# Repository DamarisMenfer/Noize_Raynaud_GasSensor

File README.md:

# MOSH
#### Arduino Project in 5th year ISS at INSA Toulouse

## Overview
This repository contains the work produced during the course of Microcontroler and Open-Source Hardware (MOSH) of the 5th year Innovative Smart Systems (ISS) at INSA Toulouse. This work was produced by Alex Noize and Mathieu Raynaud.

The aim of this project was to design a complete PCB (Printed Circuit Board) implementing a double layer transimpedance amplificator assembly. This circuit is then used plugged to an Arduino board and a LoRa antenna to collect data from a gaz sensor and send it through a LoRa network.

## Project location
The project is located [here](https://github.com/AlexNoize/MOSH/tree/master/KiCad/Shield_Gas_Sensor/Shield_Gas_Sensor_Final).

## PCB schematic
Let's first have a look to the electrical circuit:

On the center of the image, the double layer transimpedance circuit implements several functionalities: 
* On the left of the scheme, the entry resistor (R1) protect the operational amplifier from the electrostatic discharges, and is associated to the C1 capacitor to filter the voltage noise.
* The C1 capacitor is also associated to the R2 resistor to filter the current noise.
* The R3 resistor is used to adapt our assembly to the correct calibre.
* At the output of the amplifier, the C2 capacitor is associated to the R4 resistor to create an active filter.
* Then, the R5 resistor and the C4 capacitor constitute a low-pass filter at the output of the assembly.
* Finally, the C3 capacitor filter the noise coming from the 5V voltage input.

We also have 3 other schemes on the picture which are:
* The RN2483 LoRa transceiver scheme on the left-top of the scheme
* The gas sensor scheme on the top of the scheme
* The Arduino Uno shield schematic on the right of the scheme
These components are required on the scheme because they need to be considered as soon as our PCB needs to communicate with them.

## PCB footprint on KiCad
Now, let's study the footprint generated with KiCad:

On the footprint above, we made the connections between all the needed pins of our board.

To be able to put our routes on only one face of the PCB, we had to add a ground layer on the entire surface of the PCB, so that we didn't need anymore to connect the ground-connected pins each others. This was also done for economical purposes.

Finally, we can see that two pairs of pins are still not connected on the footprint. In fact, these are two pairs of pins which are directly connected to the Arduino, and they have the same potential but they are already connected through the Arduino Uno.

## PCB 3D view
Finally, here are the generated 3D views for our PCB:

## Conclusion
The knowledge acquired during our courses allowed us to create with KiCad a PCB able to be plugged on an Arduino Uno, and to receive a gas sensor and a LoRa transceiver.

Now the next step is the print of the PCB and the creation of the gas sensor to implement the complete system.

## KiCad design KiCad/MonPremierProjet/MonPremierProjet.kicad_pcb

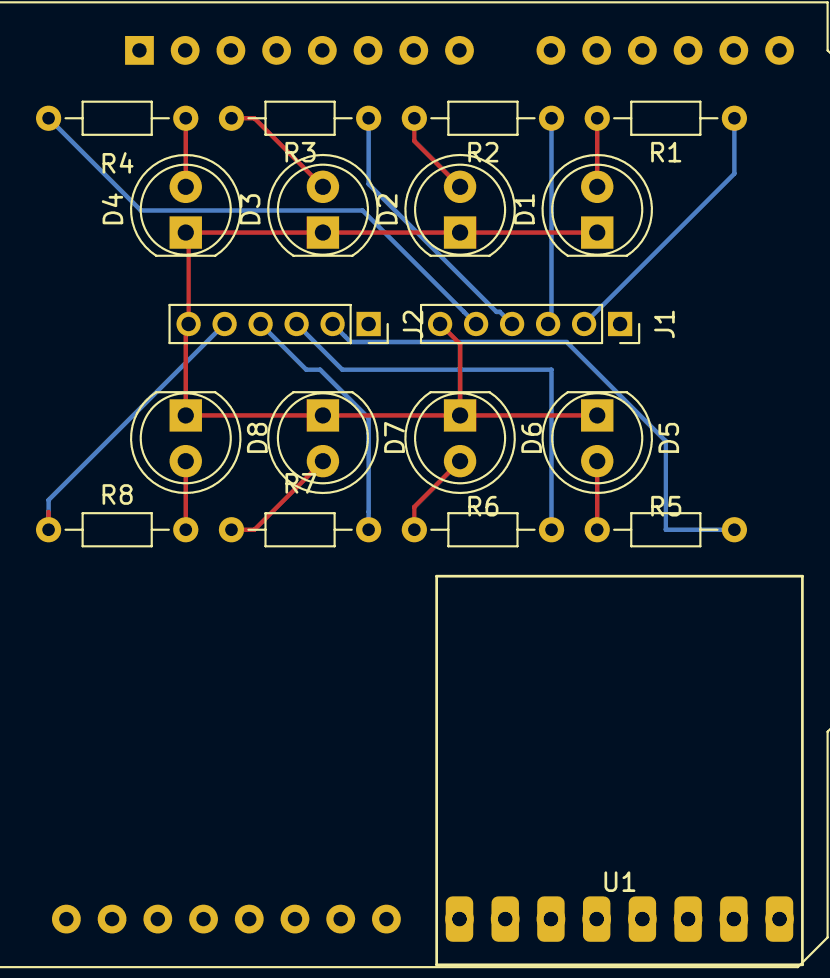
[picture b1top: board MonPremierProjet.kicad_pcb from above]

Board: 2 copper layers, 20 parts (0 on the bottom side), 18 nets.

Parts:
A1: Arduino_UNO_R2
D1, D2, D3, D4, D5, D6, D7, D8: LED; LED_D5.0mm_FlatTop
J1, J2: Conn_01x06; PinSocket_1x06_P2.00mm_Vertical
R1, R2, R3, R4, R5, R6, R7, R8: R; R_Axial_DIN0204_L3.6mm_D1.6mm_P7.62mm_Horizontal
U1: RN2483_Breakout; Rn2483 Breakout

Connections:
/CMD_LED1: J1.2, R1.1
/CMD_LED2: J1.3, R2.1
/CMD_LED3: J1.4, R3.1
/CMD_LED4: J1.5, R4.1
/CMD_LED5: J2.2, R5.1
/CMD_LED6: J2.3, R6.1
/CMD_LED7: J2.4, R7.1
/CMD_LED8: J2.5, R8.1
GND: D1.1, D2.1, D3.1, D4.1, D5.1, D6.1, D7.1, D8.1, J1.6, J2.6
unnamed: D1.2, R1.2
unnamed: D2.2, R2.2
unnamed: D3.2, R3.2
unnamed: D4.2, R4.2
unnamed: D5.2, R5.2
unnamed: D6.2, R6.2
unnamed: D7.2, R7.2
unnamed: D8.2, R8.2
VCC: J1.1, J2.1

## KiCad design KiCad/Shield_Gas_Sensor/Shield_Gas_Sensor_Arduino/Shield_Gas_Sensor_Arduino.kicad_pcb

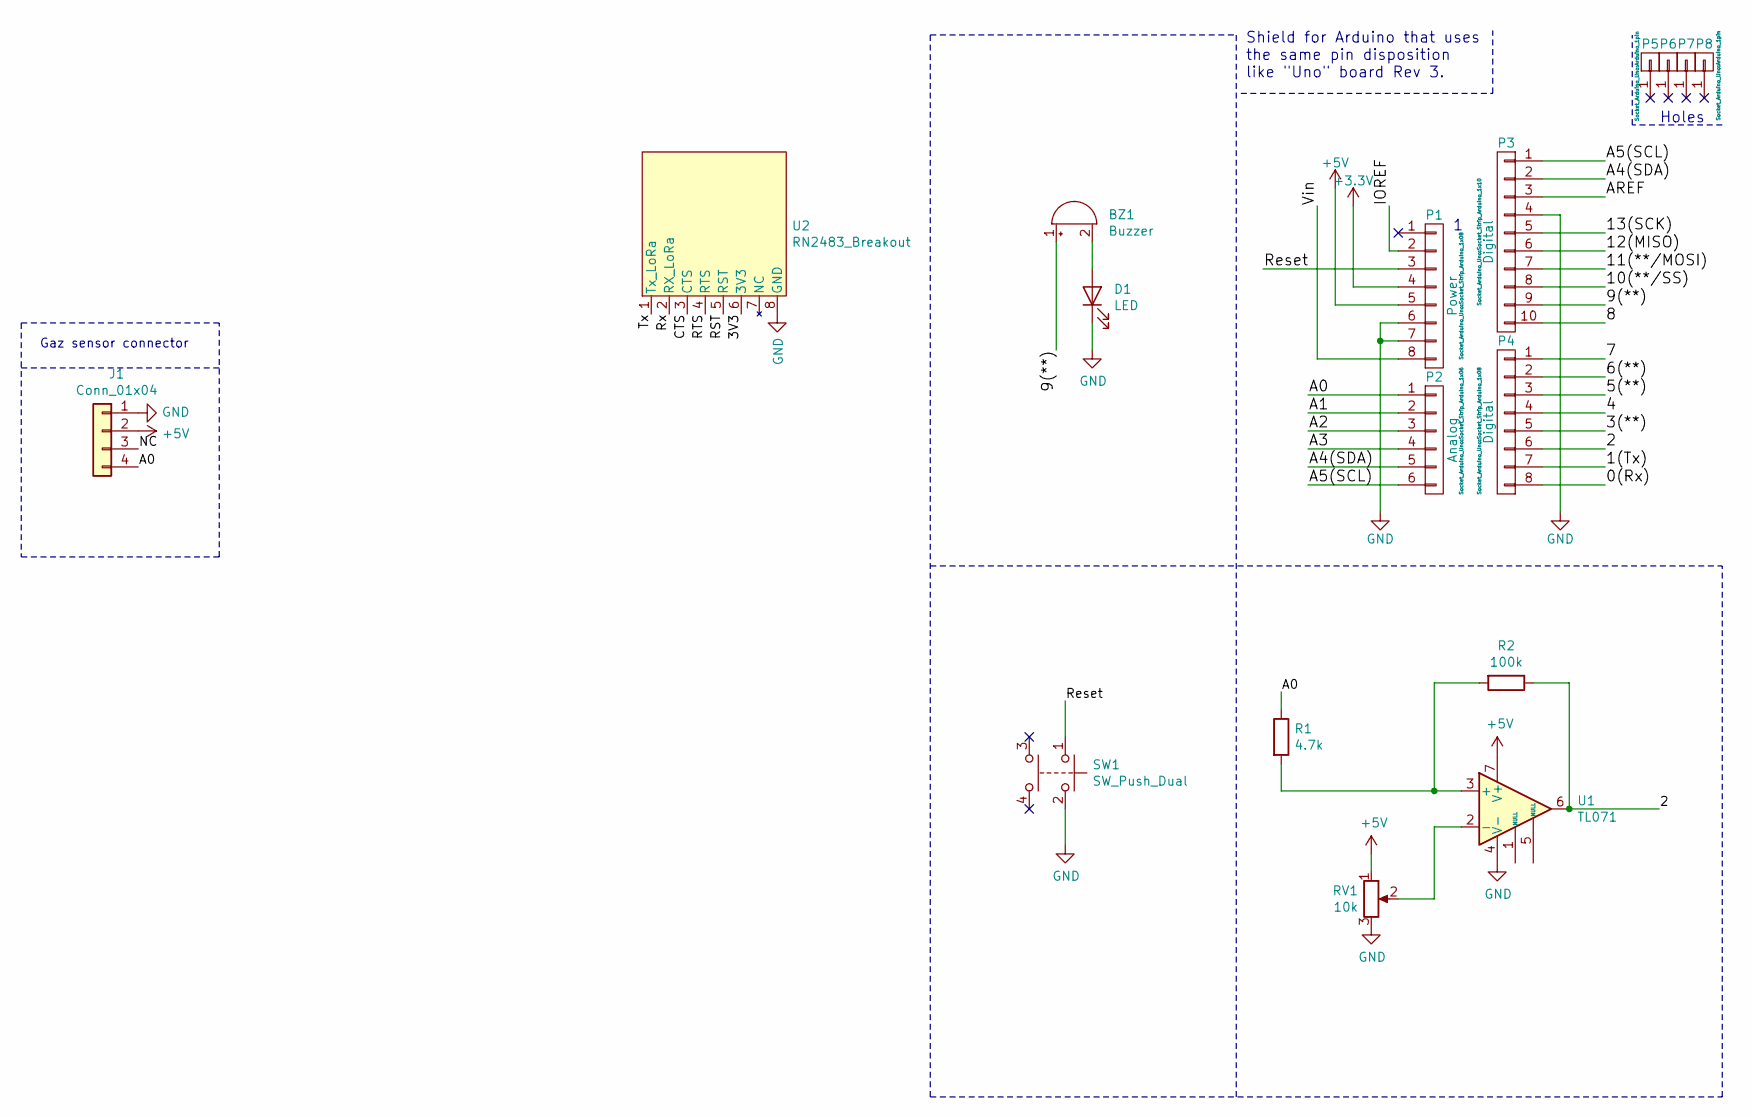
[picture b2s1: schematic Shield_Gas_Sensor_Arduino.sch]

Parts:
BZ1: Buzzer; Buzzer_12x9.5RM7.6
D1: LED; LED_D5.0mm_IRGrey
J1: Conn_01x04; JST_PH_B4B-PH-K_1x04_P2.00mm_Vertical
P1: Power; Socket_Strip_Arduino_1x08
P2: Analog; Socket_Strip_Arduino_1x06
P3: Digital; Socket_Strip_Arduino_1x10
P4: Digital; Socket_Strip_Arduino_1x08
P5, P6, P7, P8: CONN_01X01; Arduino_1pin
R1: 4.7k; R_Axial_DIN0204_L3.6mm_D1.6mm_P7.62mm_Horizontal
R2: 100k; R_Axial_DIN0204_L3.6mm_D1.6mm_P7.62mm_Horizontal
RV1: 10k; Potentiometer_ACP_CA9-V10_Vertical
SW1: SW_Push_Dual; SW_TH_Tactile_Omron_B3F-10xx
U1: TL071; TE_1-2199298-2
U2: RN2483_Breakout; Module_RN2483_Breakout

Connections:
+3V3: P1.4
+5V: J1.2, P1.5, RV1.1, U1.7 (V+)
/0(Rx): P4.8
/1(Tx): P4.7
/2: P4.6, R2.1, U1.6
/3(**): P4.5
/3V3: U2.6 (3V3)
/4: P4.4
/5(**): P4.3
/6(**): P4.2
/7: P4.1
/8: P3.10
/9(**): BZ1.1 (-), P3.9
/10(**/SS): P3.8
/11(**/MOSI): P3.7
/12(MISO): P3.6
/13(SCK): P3.5
/A0: J1.4, P2.1, R1.1
/A1: P2.2
/A2: P2.3
/A3: P2.4
/A4(SDA): P2.5, P3.2
/A5(SCL): P2.6, P3.1
/AREF: P3.3
/CTS: U2.3 (CTS)
/IOREF: P1.2
/NC: J1.3
/RST: U2.5 (RST)
/RTS: U2.4 (RTS)
/Reset: P1.3, SW1.1
/Rx: U2.2 (RX_LoRa)
/Tx: U2.1 (Tx_LoRa)
/Vin: P1.8
GND: D1.1 (K), J1.1, P1.6, P1.7, P3.4, RV1.3, SW1.2, U1.4 (V-), U2.8 (GND)
unnamed: BZ1.2 (+), D1.2 (A)
unnamed: R1.2, R2.2, U1.3 (+)
unnamed: RV1.2, U1.2 (-)

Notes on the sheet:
Holes
Shield for Arduino that uses the same pin disposition like "Uno" board Rev 3.
Gaz sensor connector

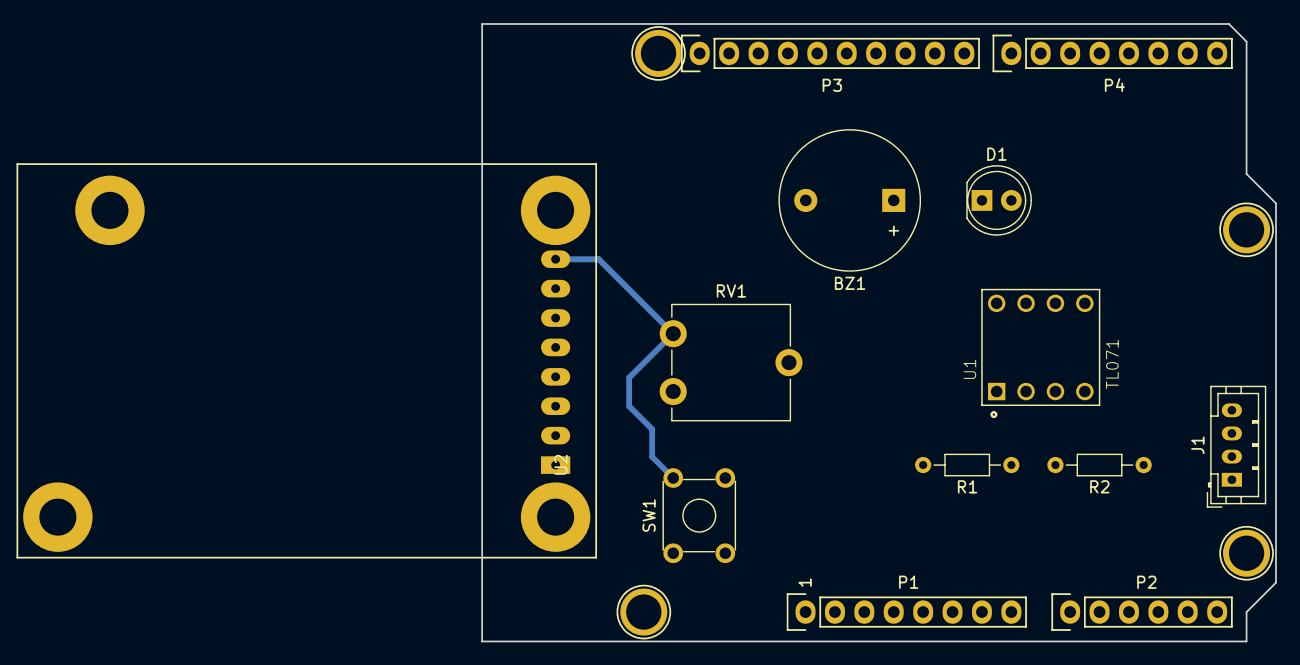
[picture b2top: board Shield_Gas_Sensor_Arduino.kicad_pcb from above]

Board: 2 copper layers, 68.6 x 53.3 mm, 17 parts (0 on the bottom side), 11 nets.

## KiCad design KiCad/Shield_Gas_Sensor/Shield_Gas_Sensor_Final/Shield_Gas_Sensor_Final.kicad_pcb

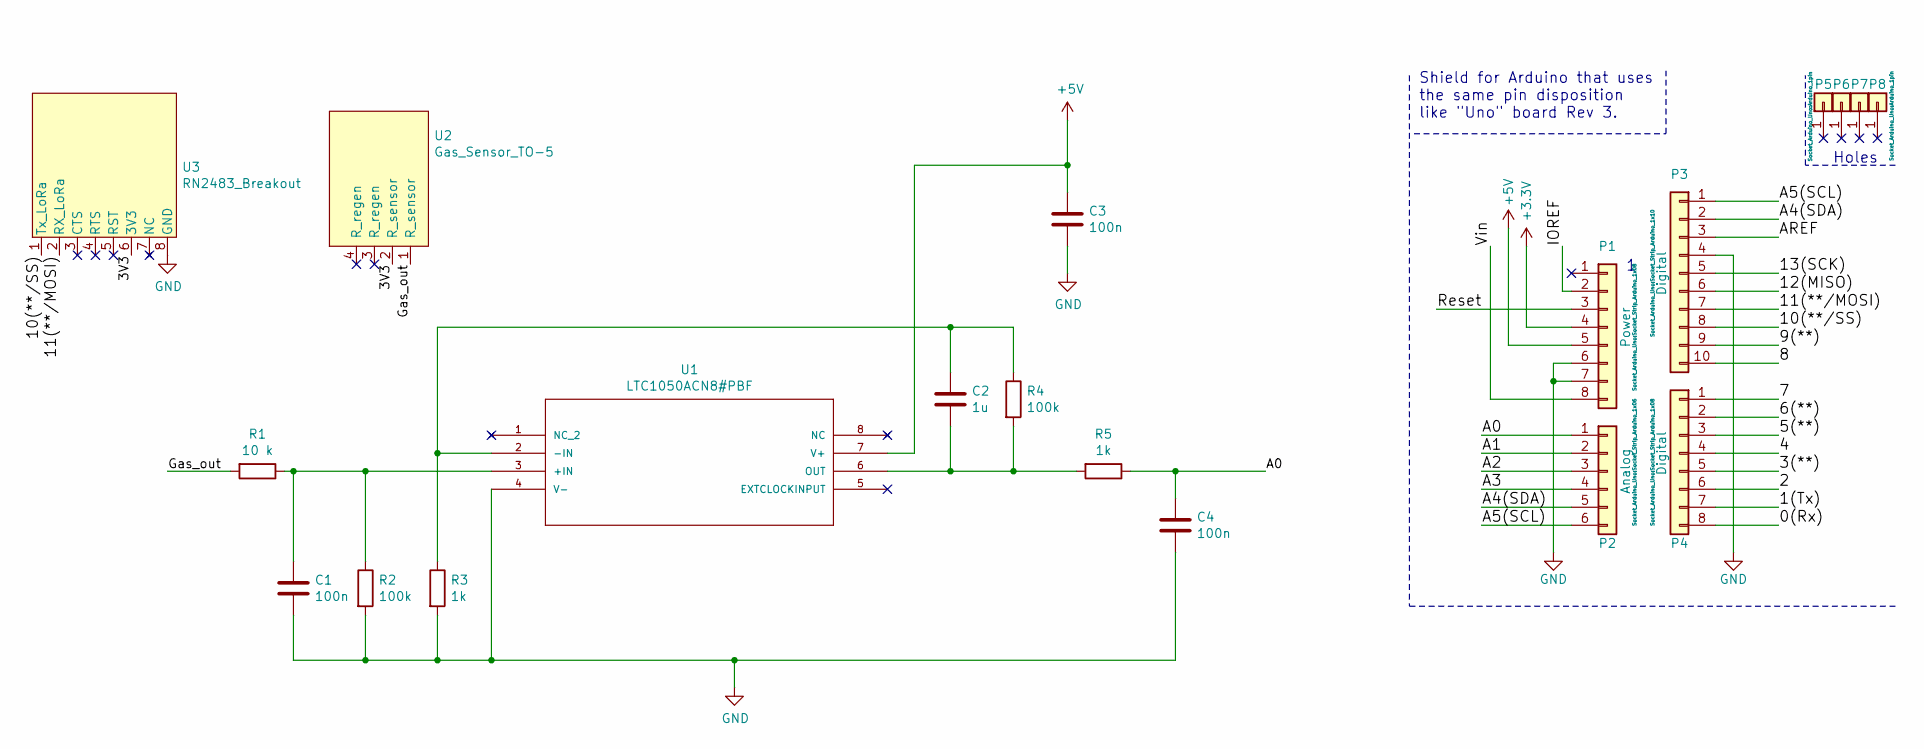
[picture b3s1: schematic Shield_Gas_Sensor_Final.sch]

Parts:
C1, C3, C4: 100n; CP_Radial_Tantal_D5.0mm_P5.00mm
C2: 1u; CP_Radial_Tantal_D5.0mm_P5.00mm
P1: Power; Socket_Strip_Arduino_1x08
P2: Analog; Socket_Strip_Arduino_1x06
P3: Digital; Socket_Strip_Arduino_1x10
P4: Digital; Socket_Strip_Arduino_1x08
P5, P6, P7, P8: CONN_01X01; Arduino_1pin
R1: 10 k; R_Axial_DIN0204_L3.6mm_D1.6mm_P5.08mm_Horizontal
R2, R4: 100k; R_Axial_DIN0204_L3.6mm_D1.6mm_P5.08mm_Horizontal
R3, R5: 1k; R_Axial_DIN0204_L3.6mm_D1.6mm_P5.08mm_Horizontal
U1: LTC1050ACN8#PBF; DIP-8_W7.62mm_LongPads
U2: Gas_Sensor_TO-5; Gas_Sensor_TO-5-4
U3: RN2483_Breakout; Module_RN2483_Breakout

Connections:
+3V3: P1.4
+5V: C3.1, P1.5, U1.7 (V+)
/0(Rx): P4.8
/1(Tx): P4.7
/2: P4.6
/3(**): P4.5
/3V3: U2.2 (R_sensor), U3.6 (3V3)
/4: P4.4
/5(**): P4.3
/6(**): P4.2
/7: P4.1
/8: P3.10
/9(**): P3.9
/10(**/SS): P3.8, U3.1 (Tx_LoRa)
/11(**/MOSI): P3.7, U3.2 (RX_LoRa)
/12(MISO): P3.6
/13(SCK): P3.5
/A0: C4.1, P2.1, R5.1
/A1: P2.2
/A2: P2.3
/A3: P2.4
/A4(SDA): P2.5, P3.2
/A5(SCL): P2.6, P3.1
/AREF: P3.3
/Gas_out: R1.2, U2.1 (R_sensor)
/IOREF: P1.2
/Reset: P1.3
/Vin: P1.8
GND: C1.2, C3.2, C4.2, P1.6, P1.7, P3.4, R2.2, R3.2, U1.4 (V-), U3.8 (GND)
unnamed: C1.1, R1.1, R2.1, U1.3 (+IN)
unnamed: C2.1, R3.1, R4.1, U1.2 (-IN)
unnamed: C2.2, R4.2, R5.2, U1.6 (OUT)

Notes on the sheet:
Holes
Shield for Arduino that uses the same pin disposition like "Uno" board Rev 3.

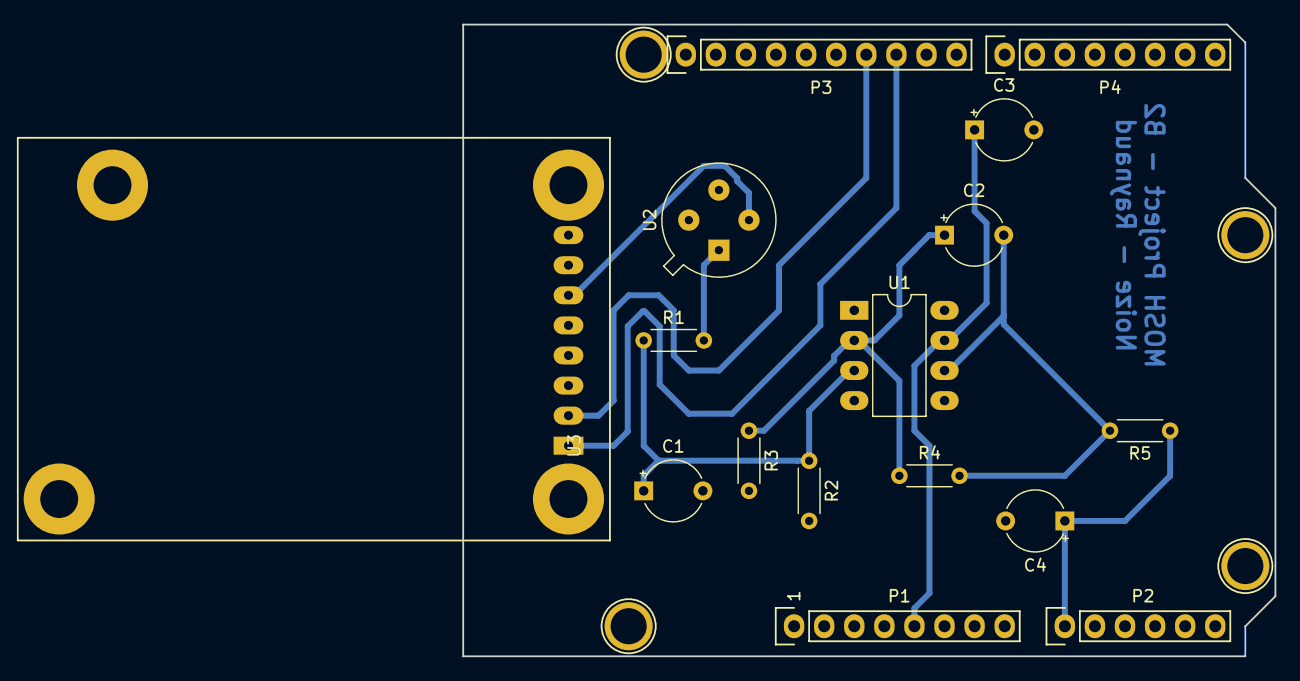
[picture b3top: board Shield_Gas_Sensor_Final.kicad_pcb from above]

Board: 2 copper layers, 68.6 x 53.3 mm, 20 parts (0 on the bottom side), 12 nets.

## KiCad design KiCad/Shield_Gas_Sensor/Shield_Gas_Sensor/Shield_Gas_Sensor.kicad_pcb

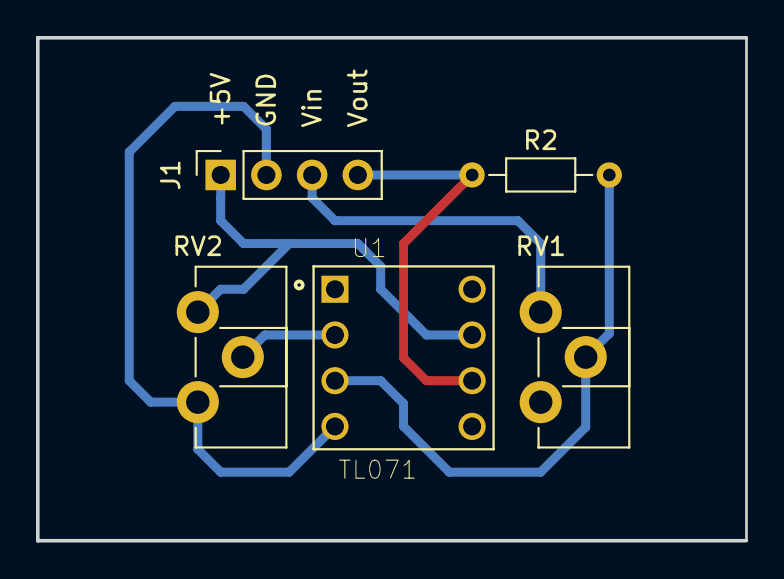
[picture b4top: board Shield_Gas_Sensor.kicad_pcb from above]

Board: 2 copper layers, 39.4 x 27.9 mm, 5 parts (0 on the bottom side), 6 nets.

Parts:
J1: Conn_01x04_Female; PinSocket_1x04_P2.54mm_Vertical
R2: 10k; R_Axial_DIN0204_L3.6mm_D1.6mm_P7.62mm_Horizontal
RV1, RV2: 10k; Potentiometer_ACP_CA9-H2,5_Horizontal
U1: TL071; TE_1-2199298-2

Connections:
+5V: J1.1, RV2.1, U1.7
/Vin: J1.3, RV1.1
/Vout: J1.4, R2.1, U1.6
/Vref: RV2.2, U1.2
GND: J1.2, RV1.3, RV2.3, U1.4
unnamed: R2.2, RV1.2, U1.3

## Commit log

2018-11-30 Main commit
